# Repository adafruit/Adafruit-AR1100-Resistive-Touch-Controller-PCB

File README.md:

## Adafruit AR1100 Resistive Touch Controller PCB
<a href="http://www.adafruit.com/products/1580"><br/>
Click here to purchase one from the Adafruit shop</a>

Getting touchy performance with your screen's touch screen? Resistive touch screens are incredibly popular as overlays to TFT and LCD displays. If you want to connect one to a computer you need something to handle the analog to digital conversion. Most converters we've found are not very easy to use, and are 'fixed' - making them difficult to calibrate. The AR1100 is a nice chip that solves this problem by acting as a touch->USB converter and also comes with calibration software. The calibration software is Windows only, but once you've calibrated you can use the screen on any OS. The AR1100 shows up as a regular Mouse or Digitizer HID device so no drivers are required. We've tested it sucessfully on Mac, Windows, and Debian Linux (Raspbian on a Raspberry Pi). Other Linux distributions may or may not work, but if you're running Linux you're probably used to that.

This breakout board features the AR1100, which has both USB and UART interfaces available. 99% of the time, you'll want to use the USB interface but there is some functionality for getting TTL UART data out (see the datasheet for details) There is also a red LED that lights up to indicate when a touch has been detected.

PCB files for the Adafruit AR1100 Resistive Touch Controller. The format is EagleCAD schematic and board layout
- https://www.adafruit.com/products/1580

### License

Adafruit invests time and resources providing this open source design, please support Adafruit and open-source hardware by purchasing products from [Adafruit](https://www.adafruit.com)!

All text above must be included in any redistribution

Designed by Limor Fried/Ladyada for Adafruit Industries.
Creative Commons Attribution/Share-Alike, all text above must be included in any redistribution. 
See license.txt for additional information.

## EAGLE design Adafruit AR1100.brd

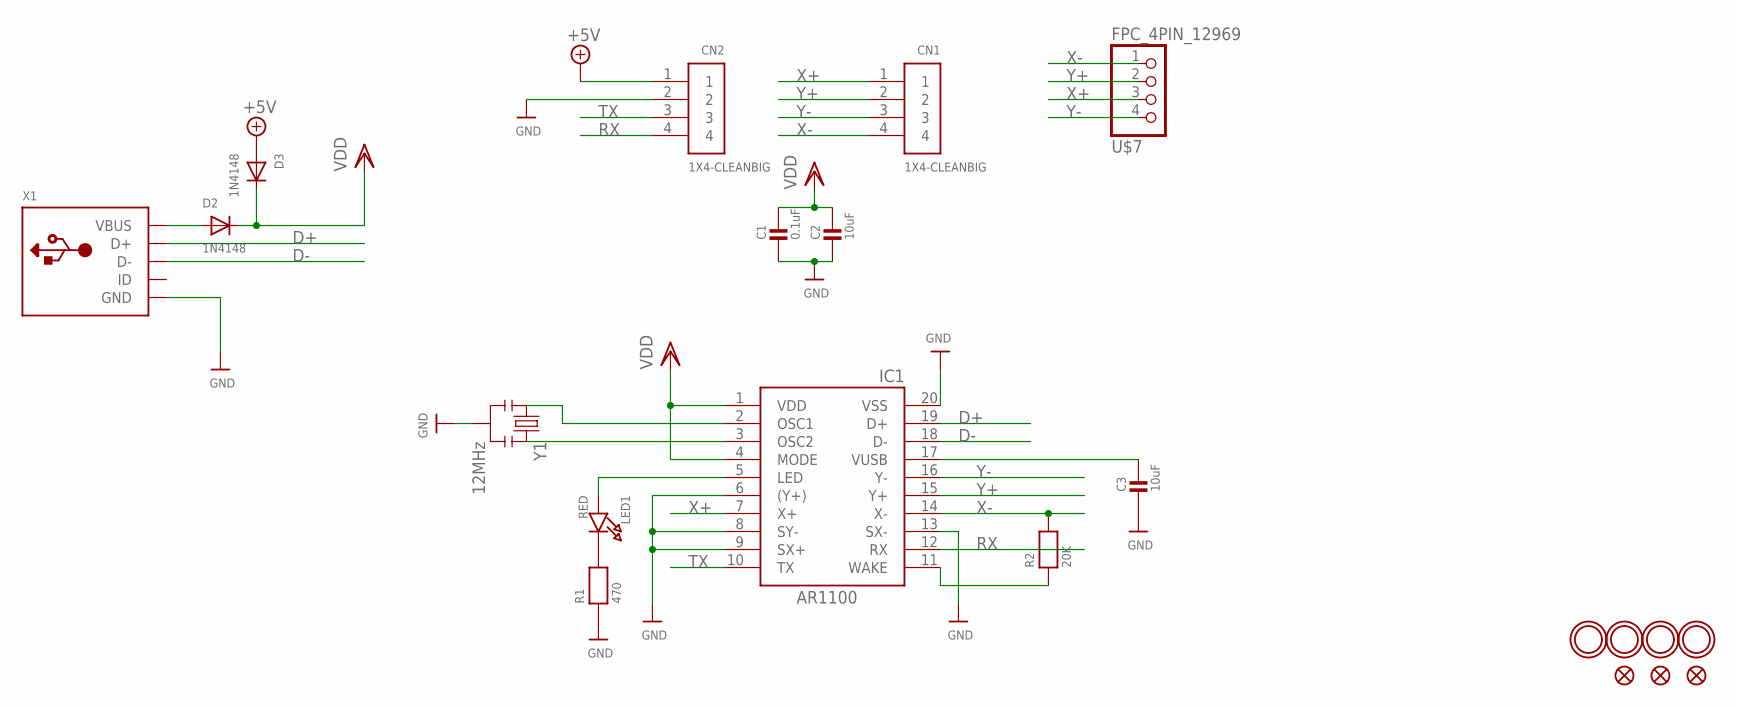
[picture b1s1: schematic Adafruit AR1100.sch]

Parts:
C1: 0.1uF; 0805-NO
C2, C3: 10uF; 0805-NO
CN1, CN2: 1X4-CLEANBIG; 1X04-CLEANBIG
D2, D3: 1N4148; SOD-323F
FID1, FID2, FID3: FIDUCIAL""; FIDUCIAL_1MM
IC1: AR1100_SSOP; TSSOP20-5.3MMBODY
LED1: RED; CHIPLED_0805_NOOUTLINE
R1: 470; 0805-NO
R2: 20K; 0805-NO
U$2, U$4, U$5, U$6: MOUNTINGHOLE2.5; MOUNTINGHOLE_2.5_PLATED
U$7: FPC_4PIN_12969; FPC_CONN_1MM_DUAL_4P
X1: USBMINIB; USB-MINIB
Y1: 12MHz; RESONATOR-SMD

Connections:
+5V: CN2.1, D3.A
D+: IC1.19 (D+), X1.D+
D-: IC1.18 (D-), X1.D-
GND: C1.2, C2.2, C3.2, CN2.2, IC1.6 ((Y+)), IC1.8 (SY-), IC1.9 (SX+), IC1.13 (SX-), IC1.20 (VSS), R1.1, X1.GND, X1.GND1 (GND), X1.GND2 (GND), X1.GND3 (GND), X1.GND4 (GND), Y1.2
unnamed: D2.A, X1.VBUS
unnamed: IC1.5 (LED), LED1.A
unnamed: LED1.C, R1.2
unnamed: C3.1, IC1.17 (VUSB)
unnamed: IC1.11 (WAKE), R2.1
unnamed: IC1.3 (OSC2), Y1.3
unnamed: IC1.2 (OSC1), Y1.1
RX: CN2.4, IC1.12 (RX)
TX: CN2.3, IC1.10 (TX)
VDD: C1.1, C2.1, D2.C, D3.C, IC1.1 (VDD), IC1.4 (MODE)
X+: CN1.1, IC1.7 (X+), U$7.3 (2)
X-: CN1.4, IC1.14 (X-), R2.2, U$7.1 (4)
Y+: CN1.2, IC1.15 (Y+), U$7.2 (3)
Y-: CN1.3, IC1.16 (Y-), U$7.4 (1)

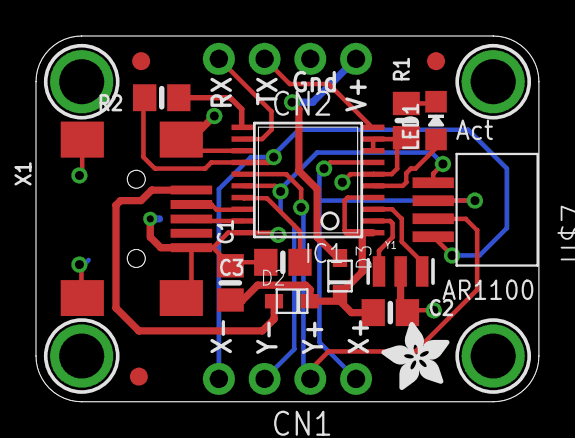
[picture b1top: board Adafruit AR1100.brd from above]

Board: 2 copper layers, 27.9 x 20.3 mm, 23 parts (1 on the bottom side), 18 nets.

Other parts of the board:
U$14: ADAFRUIT_3.5MM
U$17: ADAFRUIT_TEXT_20MM

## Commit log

2016-09-21 init

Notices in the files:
parts and their libraries:
microbuilder: This work is placed in the public domain, and may be freely used for commercial and non-commercial work with the following conditions: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
SparkFun: Licensing: CC v3.0 Share-Alike You are welcome to use this library for commercial purposes.
